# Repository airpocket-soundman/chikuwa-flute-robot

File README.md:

# ちくわ笛ロボット 強化学習環境(Arduino Physical AI チャレンジ 2026)

作品アイデア「[口笛を真似るちくわ笛ロボット](https://airpocket-soundman.github.io/maker_contest_2026/ideas/chikuwa-flute-imitation-robot/)」のための、シミュレーター・強化学習環境・学習スクリプトです。

プロジェクト全体の進め方(6 段階)と現状は [docs/roadmap.md](docs/roadmap.md) にまとめています。

> **現在の計画と結果（2026-09-24）:** 最新の構成は「**未知の機体を約9秒の較正で知り（デジタルツイン）、決定論の制御を骨格にして NN が補正と先回りを足し、同じ曲を繰り返して上手くなる**」です。
> シミュレーターの固定ベンチマーク（未知の機体32台・参照10曲）で、命中率（±25 cent・0.3 s以内）は 1回目 92 %、3回目 93 %（決定論＋ツイン 80 %、位置センサー付きの参考値 82 %）。お手本の音声を NN が聴いて覚えた目標でも 2回目 90 %。実機は未検証。
> - 計画と結果のページ: [yamabiko-plan.html](https://airpocket-soundman.github.io/chikuwa-flute-robot/yamabiko-plan.html)（決定論との比較と、曲・機体・方式を選べるシミュレーションつき）
> - 計画書: [docs/fitting-twin-plan.md](docs/fitting-twin-plan.md) ／ 実機の手順書: [docs/real_rig_runbook.md](docs/real_rig_runbook.md)
> - 主なコード: `flute_rl/yamabiko/fitting.py`（較正とツイン）、`residual_performer.py`（骨格＋NN補正）、`residual_numpy.py`（UNO Q 用の numpy 版）、`device.py`（ブラックボックス／実機の窓口）
> - これまでの試行の記録: [e2e-training-report.html](https://airpocket-soundman.github.io/chikuwa-flute-robot/e2e-training-report.html)。以下の各節はその経緯で、数値は当時のものです。

> **E2E方針（2026-09-21）:** 新しい本命経路では、YINによる音程列、物理式、固定バルブルールを推論から外し、
> 1個のモデルが生のお手本音声と生の自己音声からPWM・バルブ・終了を直接出します。
> 実装と学習手順は [docs/e2e.md](docs/e2e.md)、モデルは `flute_rl/yamabiko/e2e.py`、
> 学習は `scripts/train_yamabiko_e2e.py`、実機推論は `scripts/yamabiko_e2e_play.py` です。
> 推論経路、学習済みシミュレーターチェックポイント、NumPy書き出し、テストを実装済みです。実機評価はまだありません。
> コンテストでは、**生音声の知覚 → 物理的な行動 → 実際に鳴った生音声 → 同じモデルの内部状態の適応**という
> 閉ループ全体をフィジカルAIとして示します。笛を交換して一度崩れ、同じ重みのまま吹くほど再適応するデモを中心にします。
> UNO QではPyTorchを使わず、64,206パラメーターのモデルを約245KiBのNumPy形式へ書き出します。
> 機能優先のPC基準モデルは812,822パラメーター（約2.94MiB）で、成功後に小型版へ蒸留します。
> MCUの16kHz PCMストリームから毎10ms、最新20msを直接入力し、YINは実行しません。
> マイク・室内音響も乱数化した未学習4 seed・各64条件（合計256条件）では、音程誤差が平均 **271.6 → 277.0 → 307.6セント**、
> 自己音を遮断すると **294.3 → 326.4 → 379.3セント**です。従来モデルの乱数化時平均387.9セントから285.4セントへ改善し、閉ループ利得も平均48.0セント再現しました。反復ごとの単調な上達はまだ未達です。
> モデル構造、強化学習、採否を含む評価は [HTMLレポート](docs/e2e-training-report.html) に図解しています。
> 公開版は [GitHub Pages の段階別学習レポート](https://airpocket-soundman.github.io/chikuwa-flute-robot/e2e-training-report.html) で、各Gateの前後WAVを再生できます。

> **テーマの変更(2026-09-17): やまびこ1号。** 笛の音程を直動軸の位置センサーに使い、エンコーダーなしで位置制御する。
> 機体の違いは再帰的なモデルの記憶の中だけで覚え、吹くほど合ってくる。設計・実装・学習なしの結果は
> [docs/yamabiko.md](docs/yamabiko.md)、コードは `flute_rl/yamabiko/` と `scripts/yamabiko_*.py`。
> 以下の内容(エッジに吹き付ける笛、結果 1〜5)は旧テーマのもので、再現できるよう残しています。

- **numpy だけで動きます**(PyTorch などは不要)。Arduino UNO Q の Linux 側(Debian / Cortex-A53)でそのまま動かす前提です
- gymnasium が入っていれば `gymnasium.Env` として動作し、入っていなければ同じ API の簡易版で動きます(gymnasium 経由での動作確認はまだしていません)

## 構成

```
chikuwa-flute-robot/
├─ docs/
│  ├─ idea.md               作品アイデアのページ(元は maker_contest_2026 のアイデア集)
│  └─ uno_q_model_design.md UNO Q 向けモデル設計メモ
├─ flute_rl/
│  ├─ sim.py       物理シミュレーター(管の共鳴・リニアアクチュエーター・SCS0009・発音の窓・測定ノイズ)
│  ├─ targets.py   お手本の自動生成(カリキュラム)と、口笛の音程軌跡からの変換
│  ├─ env.py       強化学習環境(1 テイク / 複数テイク / フィードバック)と評価ツール
│  ├─ baseline.py  物理モデルだけで作った基準コントローラー(学習の出発点)
│  ├─ adapt.py     テイク間の機体推定(前のテイクの録音からアクチュエーターの速さ・管長を当てはめる)
│  ├─ policy.py    numpy の MLP 方策と、基準コントローラー + 残差の方策
│  └─ pitch.py     YIN による音程抽出(口笛入力・録音の解析用)
├─ scripts/
│  ├─ train_residual_es.py  機体推定つきコントローラーの上に残差方策を ES で学習(並列)
│  ├─ compare.py   コントローラーをテイクごとに比較(信頼区間つき)
│  ├─ train_es.py  進化戦略(ES)で残差方策を学習(旧版)
│  └─ bench.py     各処理の所要時間を測る(UNO Q 実機で実行する用)
└─ tests/          pytest
```

## すぐ試す

```bash
cd chikuwa-flute-robot
python -m pytest -q
python scripts/compare.py --takes 5 --episodes 100 --workers 8
python scripts/train_residual_es.py --feedback --takes 2 --gens 200 --pop 96 --episodes 8 --workers 8 --out runs/feedback.npz
python scripts/bench.py
```

## 環境の仕様

| 項目 | 内容 |
|---|---|
| 時間の刻み | 10ms / ステップ |
| 行動 | `[プランジャーの PWM, 吹き込み角度]`、どちらも -1〜+1(角度は ±15° に対応) |
| エピソード | お手本 1 本を `takes` 回吹く。テイクの間はプランジャーを原点に戻す |
| 風量 | 一定(モデル化していない) |

### お手本(学習用の曲)

`flute_rl/targets.py` の `make_target` が自動で作ります。演奏難易度の高すぎる曲は作りません。

| 決まり | 値 |
|---|---|
| 1 音の長さ | 0.25 秒以上(0.25 / 0.3 / 0.4 / 0.6 / 0.8 秒から選ぶ) |
| 隣の音との跳躍 | 400 セント(長 3 度程度、プランジャー約 20mm)まで |
| 奏法 | 1 曲ごとに「つなげる(スラー・同じ高さはタイ)」「切る(音の間に 50〜120ms の無音)」「混ぜる」のどれか |
| 種類(難易度順) | 1 音 → 2 音 → 2 音のグライド → 短いメロディ → ビブラートつきメロディ |

「切る」は、吹き込み角度を鳴る範囲の外に振って音を止める動きで表現します。無音の区間で鳴ると罰(`-1`)、音符で鳴らないと罰(`-2`)なので、この動きも学習の対象です。評価では、音符の間の短い無音で鳴ってしまった割合を `gap_leak` として出します。

学習では、あらかじめ作った 1,000 曲のセット(`runs/target_bank.npz`、`train_residual_es.py --bank 1000` で自動作成)から毎世代 8 曲を選んで使い回します。評価用の曲は別の乱数で作るので、学習用と重なりません。セットの中身は WAV と図で確認できます:

```bash
python scripts/export_targets.py --bank runs/target_bank.npz --count 20 --out runs/target_preview
```

### 学習する方策のネットワーク

`train_residual_es.py --feedback` で、演奏中に遅れて届く音程を使う方策を学習します。ネットワークは 3 種類から選べます。

| 指定 | 構造 | 狙い |
|---|---|---|
| `--arch mlp` | 記憶なし(今の観測だけ) | 基準 |
| `--arch mlp --history 10` | 直近 10 ステップの「聞こえたずれ・自分の PWM・角度」を窓で渡す | 遅れの情報だけを与える対照 |
| `--arch gru --hidden 16` | リカレント(GRU)。状態は曲の最初に 1 回だけ初期化し、テイクをまたいで持ち越す | 自分の指令が何ステップ後に聞こえるか(個体ごとに違う遅れ)を記憶から学ぶ |

どれも出力は「行動への補正(PWM・角度)」と「聞こえた音をどれだけ信じるか(フィードバックの強さ 0〜2 倍)」です。`scripts/trust_analysis.py` で、方策が場面ごと(休符・音の出だし・音を伸ばしている間)・遅れの長さごとにどれだけ耳を信じているかを集計できます。

### 観測

演奏中は音を聴かずに流し切る前提(案 2)なので、**標準ではリアルタイムの音程は観測に入りません**。

| ブロック | 内容 |
|---|---|
| `target` / `target_mask` | お手本の音程(今から `lookahead` ステップ先まで)と、音があるかどうか |
| `act_hist` | 直近 `history` ステップの自分の行動 |
| `travel` | 自分の PWM 指令を積算した移動量の目安 |
| `angle_readback` | SCS0009 の読み返し角度 |
| `angle_comp` | 発音補償で見つけた「鳴る角度」(唯一のキャリブレーション) |
| `time` | テイク内の経過割合 |
| `prev_err` / `prev_mask` / `prev_act` / `take` | (`takes > 1` のとき)前のテイクの音程のずれと行動。テイクを重ねて上達するための情報 |
| `fb_err` / `fb_heard` / `fb_valid` | (`feedback=True` のとき)`obs_delay` ステップ遅れて届く音程のずれ |

### 報酬(ステップごと)

| 項目 | 値 |
|---|---|
| 音程誤差 | `-min(|ずれ[セント]|, 300) / 100`(鳴るべき区間で、音程が測れたとき) |
| 無音 | 鳴るべき区間で鳴っていない: `-2` |
| 休符中の発音 | `-1` |
| 裏返り(オクターブ上) | `-1` を追加 |
| 行動の急変 | `-0.01 × |Δ行動|²` |

### ドメインランダム化(`FluteParams.sample`)

| 分類 | 項目(公称値 ± 幅) |
|---|---|
| 笛 | 管長 150±10mm、開口端補正 5±2mm、窓の位置 0±4°、窓の幅(下側 5±1.5° / 上側 4±1.5°)、窓の狭まり方、角度による音程変化 10±5 セント/°、裏返り開始位置 |
| 駆動 | 速さ 150±30mm/s(向き別)、不感帯 0.20±0.08、速度の時定数 30±15ms、指令遅れ 0〜2 ステップ、ガタ 0.3±0.2mm |
| サーボ | 速度 600±100°/s、時定数 20±10ms、刻み 300°/1024(固定) |
| 環境・測定 | 気温 25±10℃(約 3 セント/℃)、音程推定ノイズ 3±2 セント、推定の欠落 0〜4%、フィードバック遅れ 1〜5 ステップ |

値はすべて仮です。3D プリント笛・ちくわ・実機のアクチュエーターを実測して置き換えます。

## 結果 2: テイク間の機体推定(PC、2026-09-15)

`scripts/compare.py` で、学習・調整に使っていない 100 条件(カリキュラム進度 0.8)をテイクごとに比較。音程のずれの平均(セント)、[ ] は 95% 信頼区間。

| コントローラー | 1 テイク目 | 2 テイク目 | 3 テイク目 | 4 テイク目 | 5 テイク目 |
|---|---|---|---|---|---|
| 物理モデルだけ | 165 | 165 | 165 | 165 | 165 |
| 古典 ILC(ゲイン 0.7) | 165 | 69.3 [58, 83] | 38.6 [30, 48] | 30.7 [24, 39] | 26.2 [21, 33] |
| **機体推定 + ILC(`AdaptivePolicy`)** | 165 | **23.4 [19, 28]** | **22.6 [19, 27]** | **20.8 [17, 26]** | **20.3 [16, 25]** |
| 機体推定 + ILC + 残差方策(ES) | 167 | 22.0 [18, 26] | 21.9 [17, 27] | 21.9 [16, 29] | 21.4 [16, 28] |

古典 ILC との対応ありの差(機体推定 + ILC): 2 テイク目 **-45.9 セント [-58, -36]**、3 テイク目 -16.0 [-23, -10]、5 テイク目 -5.8 [-9, -3]。どのテイクでも信頼区間が 0 をまたがず、有意に良い。

仕組み(`flute_rl/adapt.py`):

- 1 テイク目のずれの大半は、**その個体のアクチュエーターの速さと管長を知らないこと**が原因だった(真のパラメーターを知っている物理モデルなら 1 テイク目でも約 40 セント)
- そこで、吹き終わった後に「自分が送った PWM」と「録音した音程」から、押し込み・引き戻しの速さ、管長、音程のずれを当てはめる(粗いグリッド探索 → ガウス・ニュートン法、外れ値の閾値を段階的に絞る)。推定した速さと真の速さの相関は約 0.96
- 次のテイクは推定したパラメーターで物理モデルを動かし、残りのずれを ILC で詰める
- 計算は numpy だけ・数十 ms で、テイクの合間に UNO Q の Linux 側で実行できる

強化学習(残差方策)について:

- 機体推定の上に残差方策(2,146 パラメーター)を並列 ES(96 候補 × 8 エピソード × 200 世代)で学習したが、**改善は 2 テイク目で -1.4 セントにとどまり、1 テイク目は +2 セント悪化**。演奏中に音を聴かない方式では、機体推定の後に残るずれは主に音の切り替わり(アクチュエーターの速さの物理的な限界)で、方策で詰められる余地が小さかった
- 前回 ES が失敗したのは、観測できない個体差(1 テイク目で ±200 セント)が評価のばらつきを支配していたため。機体推定でこれを取り除いてから学習すると、学習は安定する(悪化しない)が、伸びしろ自体が小さい

## 結果 3: 演奏中に聞いて直す方策(強化学習)

演奏中に `obs_delay` ステップ遅れて届く音程のずれで、プランジャーの推定位置を直す(`flute_rl/feedback.py`)。手作りの補正(`FeedbackPolicy`)の上に、「行動への補正」と「聞こえた音をどれだけ信じるか(補正の強さ 0〜2 倍)」を出すネットワークを ES で学習した。ネットワークは 3 種類(記憶なし MLP / 直近 10 ステップの履歴つき MLP / GRU)。お手本は 1,000 曲の固定セット(奏法の区別あり)、100 世代で打ち切り。

`scripts/compare.py --feedback --takes 3 --episodes 200`(学習に使っていない 200 条件)、音程のずれの平均(セント):

| コントローラー | 1 テイク目 | 2 テイク目 | 3 テイク目 |
|---|---|---|---|
| 物理モデルだけ | 165 | 165 | 165 |
| 古典 ILC(ゲイン 0.7) | 165 | 71 | 37 |
| 機体推定 + ILC | 165 | 19 | 18 |
| 機体推定 + 演奏中の補正(手作り) | 62 | 23 | 22 |
| + 強化学習(記憶なし MLP) | 44 | 20 | 20 |
| + 強化学習(履歴つき MLP) | **38** | 19 | 20 |
| + 強化学習(GRU) | 44 | **17** | **17** |

- 演奏中に聞くことで初めて 1 テイク目が直せる。強化学習は手作りの補正に対して 1 テイク目で約 20 セント良い(対応ありの差の信頼区間は 0 をまたがない)
- 3 種類のネットワークの差は小さく、記憶(GRU)の効果ははっきりしなかった
- 強化学習の方策は音が出ている割合が少し下がる(GRU で 0.99)。報酬の上では、大きくずれるより黙るほうが罰が軽いため

## 結果 4: 厳しめのシミュレーター(`harsh`)

聞き比べでどの方式も合格に聞こえたことから、シミュレーターが甘すぎるという指摘を受けて見直した。制御側はシミュレーターと同じ形の式を持っていて、機体推定は「値だけ違う」機体を当てはめていた。そこで、制御側が知らない効果を `FluteParams.sample(harsh=...)` で入れられるようにした:

| 分類 | 効果(`harsh=1` での範囲。すべて推測の値) |
|---|---|
| モーター | 静止摩擦(動き出しに PWM が +0〜0.15 余分に要る)、PWM と速さの非線形(指数 0.7〜1.5)、差し込むほど遅くなる(0〜30%)、演奏中の速さの揺らぎ、動きの雑音(0〜10%)、指令が 1 ステップ遅れる確率(0〜15%)、ガタ +0〜0.7mm |
| 鳴る角度 | 鳴り始めの遅れ(20〜80ms)、鳴り始めの窓が鳴り続ける窓より各側 0〜1.5° 狭い(ヒステリシス)、窓の端で確率的に音が切れる、最適な角度が差し込み量で ±3° 動く、息による音程の揺らぎ(0〜8 セント)、裏返りやすさ |
| 聞き取り | 音程の推定がオクターブずれる確率(0〜5%) |

`harsh=0` なら以前とまったく同じ機体・動きになる(テストで確認)。学習し直さずに `--harsh 1.0` で評価した結果(同じ 200 条件、**実際に鳴った音程**のずれの平均):

| コントローラー | 1 テイク目 | 2 テイク目 | 3 テイク目 |
|---|---|---|---|
| 物理モデルだけ | 172 | 174 | 173 |
| 古典 ILC(ゲイン 0.7) | 172 | 113 | 88 |
| 機体推定 + ILC | 172 | 48 | 50 |
| 機体推定 + 演奏中の補正(手作り) | 77 | 35 | 36 |
| + 強化学習(記憶なし MLP) | 59 | 27 | 28 |
| + 強化学習(履歴つき MLP) | 57 | 28 | 32 |
| + 強化学習(GRU) | 56 | 25 | 30 |

- 甘いシミュレーターと比べて、2 テイク目のずれは 1.5〜2.5 倍になり(機体推定 + ILC で 19 → 48 セント)、テイクを重ねても良くならなくなった。これまでの結果は、シミュレーターの甘さに助けられていた
- それでも順位は変わらず、機体推定・演奏中の補正・強化学習のそれぞれに効果は残っている
- 最初は測った音程(音程推定のオクターブ誤りを含む)で評価していて、2 テイク目を 58〜79 セントと大きく見積もっていた。上の表は実際に鳴った音程で数え直したもの
- 厳しいシミュレーターでの学習し直しは GPU 版(`scripts/train_es_gpu.py --harsh 1.0`)で進めている

## 結果 5: 厳しいシミュレーターでの学習し直しと、耳で聞く方策(E2E 方法 A)

`scripts/train_es_gpu.py --harsh 1.0` で 3 つの方策を 100 世代学習し直した(甘い機体で学習したモデルから開始)。E2E の方法 A(`--hearing runs/pitchnet_self.pt`)では、シミュレーターの中で笛の音を鳴らし(8kHz、`flute_rl/torch_audio.py`)、学習済みの耳のネットワークで `obs_delay` 遅れて聞かせる。演奏中の補正と機体推定には耳が聞き取った音程を使い、方策には耳の自信の度合いと特徴の要約(PCA 16 次元)も渡す。

`scripts/compare_gpu.py --harsh 1.0 --takes 3 --episodes 200`(学習に使っていない 200 条件)、**実際に鳴った音程**のずれの平均(セント)。( ) は測った音程でのずれ(音程推定のオクターブ誤りを含む):

| コントローラー | 1 テイク目 | 2 テイク目 | 3 テイク目 | 音が出ている割合 |
|---|---|---|---|---|
| 手作りの補正(測定値で聞く) | 73.7 (104.0) | 35.4 (66.6) | 34.5 (64.9) | 0.96 |
| 手作りの補正(耳で聞く) | 79.7 (109.6) | 36.4 (65.4) | 35.1 (67.5) | 0.96 |
| 甘い機体で学習: 記憶なし MLP / 履歴つき MLP / GRU | 58.6 / 56.9 / 56.4 | 26.5 / 27.7 / 25.2 | 28.0 / 31.6 / 29.9 | 0.94 / 0.93 / 0.92 |
| 学習し直した後: 記憶なし MLP | 58.4 | 31.1 | 32.2 | 0.96 |
| 学習し直した後: 履歴つき MLP | **53.6** | **24.9** | **26.7** | 0.96 |
| 学習し直した後: GRU | 56.0 | 26.4 | 30.5 | 0.96 |
| 学習し直した後: GRU(耳で聞く、方法 A) | 62.3 | 26.9 | 28.0 | 0.96 |

学習し直した履歴つき MLP は、手作りの補正に対して 1〜3 テイク目で -20.1 / -10.5 / -7.8 セント(対応ありの差、信頼区間は 0 をまたがない)。

- 耳は測定値の代わりに使える(手作りの補正で比べて、差は信頼区間の範囲内)
- 学習し直しの伸びは約 3 セントと小さい。変わったのは、黙って点を稼ぐ癖が消えたこと(音が出ている割合が 0.96 に戻った)
- 耳の特徴を渡しても(方法 A)、はっきりした効果はなかった
- `scripts/trust_analysis.py --harsh 1.0` で見ると、GRU は耳を信じる度合いを場面や遅れによらず約 1.8 倍にしているだけ
- 厳しい効果を 1 つずつ入れて調べると、測った音程のずれを押し上げていた最大の要因は**音程推定のオクターブ誤り**だった(2 テイク目 26 → 56 セント)。これは実際に鳴った音のずれではなく、測り間違い。以前は測った音程で評価していたので、厳しいシミュレーターのずれを大きく見積もっていた(今は実際に鳴った音程で評価する)
- 制御側が乱数を使わない厳しい効果(不感帯・静止摩擦・非線形・差し込み量で変わる速さ)の真の値を知っていても、2 テイク目の改善は 8〜9 セントまで。機体推定のモデルを広げる伸びしろは限られる
- 次は、実物の測定でシミュレーターを合わせ込むこと

## 実物の笛でシミュレーターを合わせ込む

シミュレーターの値は今はすべて推測なので、3D プリント笛(やちくわ)を測って置き換える。録音は WAV(16bit か 32bit の PCM)。スマホの録音は `ffmpeg -i rec.m4a -ac 1 -ar 48000 take.wav` などで変換する。

**1. 1 本の録音を調べる**(何 Hz で鳴っているか、倍音か):

```bash
python scripts/analyze_recording.py take.wav --tube-mm 60 --bore-mm 10 --temp 25
```

**2. 差し込み量を変えて測る(管の合わせ込み)**: 底(プランジャーや詰め物)の差し込み量を 5〜10mm ずつ変え、同じ吹き方で 1 本ずつ録音する。`depth_mm,ファイル名` の CSV を作って:

```bash
python scripts/calibrate.py tube sweep_depth.csv --bore-mm 10
```

管の実効長と音速(気温の目安)、各点のずれ(セント)と、`FluteParams` の `tube_len` / `end_corr` / `temp_c` の値を出す。

**3. 角度を変えて測る(鳴る角度の合わせ込み)**: 差し込み量を固定し、吹き込む角度を 0.5〜1° ずつ変えて録音する。`angle_deg,ファイル名` の CSV を作って:

```bash
python scripts/calibrate.py window sweep_angle.csv
```

鳴る範囲の端と中心、角度 1° あたりの音程の変化(`theta_opt_deg` / `win_lo_deg` / `win_hi_deg` / `k_theta`)を出す。

**4. PWM を変えて動かす(アクチュエーターの合わせ込み)**: 笛を鳴らしたまま、一定の PWM でプランジャーを動かして録音する。PWM を何段階か変えて(押し込む向きと引き戻す向きは別々に)、`pwm,ファイル名` の CSV を作る。2 の結果(実効長と音速)を渡して:

```bash
python scripts/calibrate.py actuator sweep_pwm.csv --acoustic-mm 150.5 --sound-speed 346.4
```

音程の変化を位置の変化に直して速さを求め、最大の速さ・不感帯・PWM と速さの非線形(`v_max_in` / `deadband` / `pwm_curve`)を出す。

どれも、シミュレーターで作った「答えの分かっている録音」から値を取り戻せることをテストで確かめてある(`tests/test_calibrate.py`)。

## 段階 2・3 の準備(小さくする、マイコンで動かす)

実機がなくても PC でできるところまで進めた。UNO Q の実機では、どれもまだ試していない。

| 項目 | 内容 | 結果 |
|---|---|---|
| 方策の int8 化 | `scripts/quantize_policy.py`。行列ごとに 1 つのスケールで int8 にし、C のヘッダーを書き出す | 履歴つき MLP(3,267 パラメーター)が 3,380 バイトに収まる。厳しい機体 200 台で float32 との差は 0.0 ± 0.1 セント |
| 小さい耳 | `PitchNet(width=8, pool=4)`、20 セント刻み | 16,131 パラメーター、1 フレーム 0.18M 回の積和(大きい耳は 250,277 / 2.41M)。合成音で誤差の中央値 1.0 セント(大きい耳 0.9、YIN 3.1)。10ms ごとに動かすと 1 秒あたり約 1,800 万回の積和で、マイコンの CPU の 1 割前後の見込み(実機で要計測) |
| 制御の C 版 | `mcu/controller.{h,c}`、`mcu/policy_mlp.{h,c}` | 物理モデル・演奏中の補正・ILC・int8 の方策を 1 台分。機体推定はテイクの合間に Linux 側で行い、値だけ渡す。雑音のない機体で numpy 版と同じ行動(テスト) |
| HIL の通信 | `mcu/hil_protocol.{h,c}`、`scripts/hil.py` | テイクの頭にお手本・前回のずれ・推定した機体をまとめて送り、10ms ごとには 13 バイトずつやり取りする(115200 baud で約 2.3ms)。PC 上の代役(`mcu/hil_host.c`)を相手に、numpy 版と同じ演奏になる(テスト) |
| Arduino スケッチ | `mcu/uno_q_hil/uno_q_hil.ino` | 実機未確認。どのシリアルが PC や Linux 側につながるかは、実機で確かめる必要がある |

```bash
python scripts/quantize_policy.py runs/harsh_hist.npz --out runs/harsh_hist_int8
python -m ziglang cc -O2 -Imcu -Iruns -DHIL_NET_HEADER='"harsh_hist_int8.h"' -DHIL_NET=HARSH_HIST_INT8 mcu/hil_host.c mcu/hil_protocol.c mcu/controller.c mcu/policy_mlp.c -o runs/hil_host.exe
python scripts/hil.py --link process:runs/hil_host.exe --history 10 --harsh 1.0
```

C のテストには、C コンパイラーの入った `ziglang`(`pip install ziglang`)を使う。

## GPU 版(`flute_rl/torch_sim.py`、`flute_rl/torch_env.py`)

多数の機体をまとめて 1 ステップずつ進める版。雑音のない機体では、行動が numpy 版と 1 ステップずつ一致する(GRU を含む)。1 世代 768 回の演奏では CPU 20 コアの numpy 版とほぼ同じ速さ(約 6 秒)で、候補を 10 倍にすると 1 秒あたりの演奏数が約 2.3 倍になる。細かい計算の呼び出しが時間を決めているので、さらに速くするには計算をまとめる工夫が要る。

開発の経緯と、世代ごとの演奏の聞き比べは [docs/history.html](docs/history.html) にある。

## 結果 1: 最初の実験(PC、2026-09-15 時点)

ランダム化した 20 条件(カリキュラム進度 0.8)での、音程のずれの平均(セント)。

| コントローラー | 1 テイク目 | 2 テイク目 | 3 テイク目 | 4 テイク目 | 5 テイク目 |
|---|---|---|---|---|---|
| 物理モデルだけ(`PhysicsPriorPolicy`) | 202 | 202 | 202 | 202 | 202 |
| + 古典 ILC、ゲイン 0.5(`ILCPolicy`) | 202 | 118 | 78 | 63 | 52 |
| + 古典 ILC、ゲイン 0.7 | 202 | 90 | 61 | 51 | 44 |
| + 古典 ILC、ゲイン 0.9 | 202 | 77 | 54 | 49 | 45 |
| 物理モデル + ES 残差(40 世代、学習率 0.03) | 333 | 175 | 298 | - | - |
| ILC(ゲイン 0.7)+ ES 残差(25 世代、学習率 0.005、σ 0.02) | 212 | 82 | 61 | - | - |

分かったこと:

- アクチュエーターの速さの個体差(±20%)があると、音を聴かずに推測で動かすだけでは 1 テイク目が平均 200 セントずれる。1 テイク目の中ではこの個体差を知る手段がない
- 前のテイクのずれを観測に入れれば、古典的な ILC だけでもテイクごとに上達する(5 テイクで 202 → 44 セント)。環境の設計どおりに動いている
- **ES による残差方策の学習は、最初の設定では失敗した**(物理モデルより悪化)。評価のばらつき(1 候補あたり 4 エピソード)に対して更新が大きすぎたと考えられる。学習率・ノイズを下げ、出発点を ILC にした再学習では悪化はしなくなったが、ILC だけ(202 / 90 / 61)と比べて**有意な改善もなかった**(2 テイク目がわずかに良く、1 テイク目がわずかに悪い程度で、評価のばらつきの範囲)
- 今の ES(1 世代 16 候補 × 数エピソード)では、7,400 パラメーターの方策を動かすには評価が粗すぎる。次の手は、候補数・エピソード数を増やして並列化する、観測を絞って方策を小さくする、ILC のゲインなど数個のパラメーターだけを学習させる、のいずれか

## 次にやること

- 実機ログから `FluteParams` を当てはめる(世界モデルの実測合わせ)と、残差モデルの追加
- フィードバック補正方策(`feedback=True`)の学習と、MCU に載せる小型化
- 口笛の録音 → `pitch.pitch_track` → `targets.from_pitch_track` → 方策、の一連の流れを実機で通す

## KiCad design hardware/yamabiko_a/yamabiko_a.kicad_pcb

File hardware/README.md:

# やまびこ1号の基板（KiCad 10）

| フォルダ | 中身 |
|---|---|
| `yamabiko_a/` | **A 基板**: UNO Q の R3 ヘッダーに挿す Arduino シールド（外形は Arduino Uno、ねじ穴なし）。リニアアクチュエーター（TB6643KQ）、ファン（ハイサイドスイッチ、PWM、タコ）、SCS0009（6 V レギュレーター、半二重バッファ）、控えの電磁弁、演奏開始ボタン |
| `yamabiko_b/` | **B 基板**: UNO Breakout Carrier の J14 / J15 に載せるマイク基板。ICS-43434 を MCU の SAI1（3.3 V）へ、予備で MI2S0（1.8 V）へ。**J14 の左には何も出さない**（UNO Q が載る）: 基板の左端は J14 のすぐ外で切り、部品は J15 の右に並べて、Carrier の右端から 13 mm はみ出す。マイクの L/R は GND 固定（左スロット）。予備に I2C（J15-16 / 18 = PF14 / PF15、4.7 kΩ プルアップ）と ADC / GPIO（PA0 / PA1 / PA3）を XH で出す |
| `lib/` | プロジェクトのシンボルとフットプリント（TB6643KQ、ピン番号 1 = G / 2 = D / 3 = S の FET） |
| `gen/` | 上の 2 つを作るスクリプト |

部品はすべて秋月電子通商のスルーホール品、コネクターは XH。部品表と IO 仕様は公開ページにまとめてある
（部品表: <https://claude.ai/artifact/Dvwt1oD2amMsziMAJQZxBU>、IO 仕様: <https://claude.ai/artifact/3YuJc5qp5sogrEiBCrkaD5>）。

## 作り方

回路図と基板は手で描いていない。**`gen/design.py` の部品・ネット・配置が正**で、そこから生成する。

```
gen/build.sh FREEROUTING.jar REPORT_DIR
```

1. `gen_boards.py`（KiCad の Python）: `design.py` から回路図を書き、KiCad にネットリストを出させて `design.py` と照合してから、
   同じネットで基板を作る。A 基板の外形と R3 ヘッダーの位置は KiCad の `Arduino_Uno` テンプレートのもの
2. `route.py`: Specctra DSN を書き出して [Freerouting](https://github.com/freerouting/freerouting)（v2.4.1 を使用。リポジトリには入れていない）で自動配線し、
   結果を取り込んで両面に GND ベタを張る
3. `finish_route.py`: Freerouting が残した接続があれば、2 層の格子上の A* で引く
4. `check.sh`: ERC、DRC（回路図との一致を含む）、配置図

版だけ上げるときは、`design.py` の `REV` を変えて `gen/add_title.py yamabiko_a/yamabiko_a.kicad_pcb` を KiCad の Python で実行すれば、配線し直さずにシルクの版の表記だけ入れ替わる（回路図の表題欄の rev は手で直す）。

シルクには全部品の部品番号と、抵抗・コンデンサの値を入れる（電解コンデンサは容量だけ。耐圧は部品表）。XH コネクターと SW1 は部品番号に接続先の名前を添え（例: `J3 FAN`）、コネクターは各パッドの脇にピン名を入れる（`design.py` の `device` / `pin_names`）。UNO Q のヘッダー J101〜J104 の番号はシルクに出さない。基板名と版（`Yamabiko No.1 A Rev 1.0` など。版は `design.py` の `REV`）も表面のシルクに入れ、部品・パッド・シルク・基板の端から離れた空きのうち、基板の中央にいちばん近いところに置く（入る最大の文字サイズで、入らなければ 2 行）。文字の位置は `gen_boards.py` が部品ごとに上下左右などの候補から、パッド・シルクの図形・ほかの文字・基板の端と重ならないところを選ぶ。

生成した時点の結果（2026-09-18）: 両基板とも ERC 0、DRC のエラー 0、未接続 0、回路図との不一致 0。
警告は A 基板で、シルクが基板の端に近い 2 件と、R8 / R9 の値がヘッダー J101 の枠線にかかる 2 件、GND ベタのサーマルの本数。

KiCad の Python（pcbnew）には落とし穴がある: 読み込んだ基板から `Remove` すると、そのプロセスではそれ以降の SWIG の
ラッパーが壊れる（`SwigPyObject` が返る）。スクリプトはすべて、削除を pcbnew ではなくファイル側で行う。
また、基板を保存すると `.kicad_pro` が既定のネットクラスで上書きされるので、プロジェクトファイルは基板の後に書く。

## 発注（JLCPCB）

`gen/fab.sh` がガーバーとドリルを出して、基板ごとに zip にまとめる（`fab/yamabiko_a_gerber.zip`、`fab/yamabiko_b_gerber.zip`）。
出す前にベタを塗り直し、シルクはレジストの開口で切る。JLCPCB にはこの zip をそのまま上げる。

| | A 基板 | B 基板 |
|---|---|---|
| 大きさ | 68.6 × 53.3 mm（Arduino Uno 形、角の面取りあり） | 40.7 × 53.3 mm |
| 層 | 2 | 2 |
| 最小の線幅 / 間隔 | 0.3 / 0.2 mm | 0.3 / 0.2 mm |
| 最小の穴 | 0.4 mm（ビア 0.8 mm、4 個） | 0.8 mm（ビアなし） |
| 長穴 | DC ジャック J1 に 3 個 | なし |

ほかは JLCPCB の既定（厚み 1.6 mm、有鉛 HASL でも無鉛でも可、レジストの色は自由）でよい。
KiCad で基板を直したら `gen/check.sh` を通してから `gen/fab.sh` をやり直す。

## 組み立ての注意

- **A 基板の R3 ヘッダー**: 3D 表示では上向きに立っているが、実物はオスのピンヘッダーを上から挿してピンを下に出し、UNO Q のソケットに挿す
- **B 基板の J14 / J15**: 3D 表示ではオスヘッダーだが、実物は **2×20 のメスのピンソケットを裏（下面）に付けて** Carrier の J14 / J15 にかぶせる。
  パッドの並びは Carrier の上面図と同じ（上から見て奇数ピンが左列、1 番ピンが上端）
- **B 基板の J2 は 1.8 V**（MI2S0）。3.3 V の線をつながない
- **B 基板の予備 I2C（J3）** は PF14 / PF15。UNO Q の Arduino コアの既定の I2C4 は PD12 / PD13 なので、使うときはピンの割り当てを切り替える
- **TB6643KQ の裏の金属部分**は IC の GND（4 番ピン）とつながっている。4 番ピンは検出抵抗 R1 を通って GND に落ちるので、放熱器を付けるなら絶縁する
- **2N7000（Q2, Q3）** は足を 2.54 mm に広げて挿す（フットプリントが `TO-92_Inline_Wide`）
- 控えの電磁弁まわり（Q4, R15, R16, D1, J5）は DNP。必要になったら実装する

## まだ決めていないこと

- アクチュエーターの実際の電流（TB6643KQ の平均 1.5 A に収まるか）。検出抵抗 R1（0.1 Ω）の電圧で測れる
- U2（NJM7806FA）の放熱器。基板上に場所を取っていないので、まず放熱器なしで温度を見る

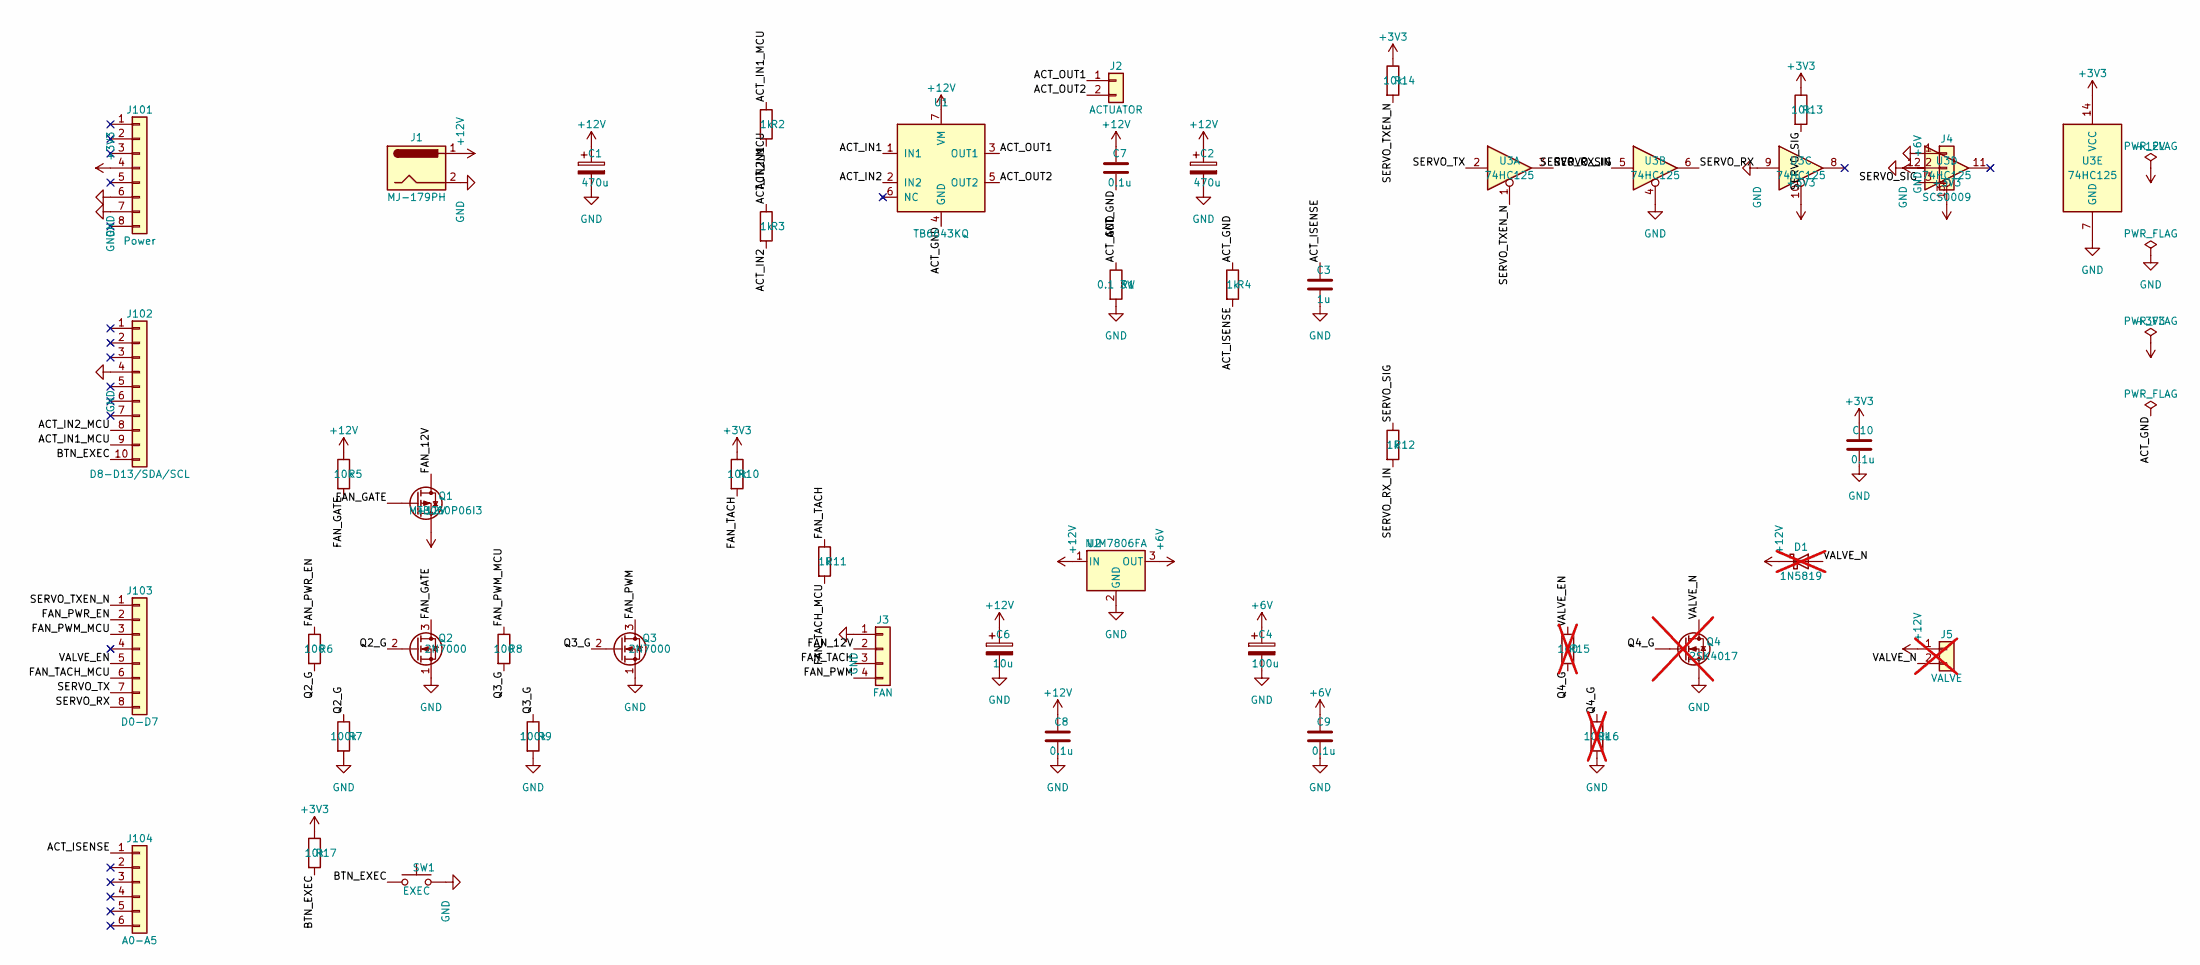
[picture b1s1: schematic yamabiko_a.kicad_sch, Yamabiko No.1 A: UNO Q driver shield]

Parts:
C1, C2: 470u; CP_Radial_D10.0mm_P5.00mm
C3: 1u; C_Disc_D5.0mm_W2.5mm_P5.00mm
C4: 100u; CP_Radial_D6.3mm_P2.50mm
C6: 10u; CP_Radial_D5.0mm_P2.00mm
C7, C8, C9, C10: 0.1u; C_Disc_D3.0mm_W1.6mm_P2.50mm
D1: 1N5819; D_DO-41_SOD81_P5.08mm_Vertical_AnodeUp; not fitted
J1: MJ-179PH; BarrelJack_Horizontal
J2: ACTUATOR; JST_XH_B2B-XH-A_1x02_P2.50mm_Vertical
J3: FAN; JST_XH_B4B-XH-A_1x04_P2.50mm_Vertical
J4: SCS0009; JST_XH_B3B-XH-A_1x03_P2.50mm_Vertical
J5: VALVE; JST_XH_B2B-XH-A_1x02_P2.50mm_Vertical; not fitted
J101: Power; PinHeader_1x08_P2.54mm_Vertical
J102: D8-D13/SDA/SCL; PinHeader_1x10_P2.54mm_Vertical
J103: D0-D7; PinHeader_1x08_P2.54mm_Vertical
J104: A0-A5; PinHeader_1x06_P2.54mm_Vertical
Q1: MTB060P06I3; TO-251-3_Vertical
Q2, Q3: 2N7000; TO-92_Inline_Wide
Q4: 2SK4017; TO-251-3_Vertical; not fitted
R1: 0.1 3W; R_Axial_DIN0516_L15.5mm_D5.0mm_P20.32mm_Horizontal
R2, R3, R4, R11, R12: 1k; R_Axial_DIN0207_L6.3mm_D2.5mm_P2.54mm_Vertical
R5, R10, R13, R14, R17: 10k; R_Axial_DIN0207_L6.3mm_D2.5mm_P2.54mm_Vertical
R6, R8: 100; R_Axial_DIN0207_L6.3mm_D2.5mm_P2.54mm_Vertical
R7, R9: 100k; R_Axial_DIN0207_L6.3mm_D2.5mm_P2.54mm_Vertical
R15: 100; R_Axial_DIN0207_L6.3mm_D2.5mm_P2.54mm_Vertical; not fitted
R16: 100k; R_Axial_DIN0207_L6.3mm_D2.5mm_P2.54mm_Vertical; not fitted
SW1: EXEC; SW_PUSH_6mm
U1: TB6643KQ; Toshiba_HSIP7_P2.54mm
U2: NJM7806FA; TO-220F-3_Vertical
U3: 74HC125; DIP-14_W7.62mm_Socket

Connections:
+3V3: C10.1, J101.4, R10.1, R13.1, R14.1, R17.1, U3.10, U3.13, U3.14 (VCC)
+6V: C4.1, C9.1, J4.2, U2.3 (OUT)
+12V: C1.1, C2.1, C6.1, C7.1, C8.1, D1.1 (K), J1.1, J5.1, Q1.3 (S), R5.1, U1.7 (VM), U2.1 (IN)
/ACT_GND: C7.2, R1.1, R4.1, U1.4 (GND)
/ACT_IN1: R2.2, U1.1 (IN1)
/ACT_IN1_MCU: J102.9, R2.1
/ACT_IN2: R3.2, U1.2 (IN2)
/ACT_IN2_MCU: J102.8, R3.1
/ACT_ISENSE: C3.1, J104.1, R4.2
/ACT_OUT1: J2.1, U1.3 (OUT1)
/ACT_OUT2: J2.2, U1.5 (OUT2)
/BTN_EXEC: J102.10, R17.2, SW1.1
/FAN_12V: J3.2, Q1.2 (D)
/FAN_GATE: Q1.1 (G), Q2.3 (D), R5.2
/FAN_PWM: J3.4, Q3.3 (D)
/FAN_PWM_MCU: J103.3, R8.1
/FAN_PWR_EN: J103.2, R6.1
/FAN_TACH: J3.3, R10.2, R11.1
/FAN_TACH_MCU: J103.6, R11.2
/Q2_G: Q2.2 (G), R6.2, R7.1
/Q3_G: Q3.2 (G), R8.2, R9.1
/Q4_G: Q4.1 (G), R15.2, R16.1
/SERVO_RX: J103.8, U3.6
/SERVO_RX_IN: R12.2, U3.5
/SERVO_SIG: J4.3, R12.1, R13.2, U3.3
/SERVO_TX: J103.7, U3.2
/SERVO_TXEN_N: J103.1, R14.2, U3.1
/VALVE_EN: J103.5, R15.1
/VALVE_N: D1.2 (A), J5.2, Q4.2 (D)
GND: C1.2, C2.2, C3.2, C4.2, C6.2, C8.2, C9.2, C10.2, J1.2, J3.1, J4.1, J101.6, J101.7, J102.4, Q2.1 (S), Q3.1 (S), Q4.3 (S), R1.2, R7.2, R9.2, R16.2, SW1.2, U2.2 (GND), U3.4, U3.7 (GND), U3.9, U3.12

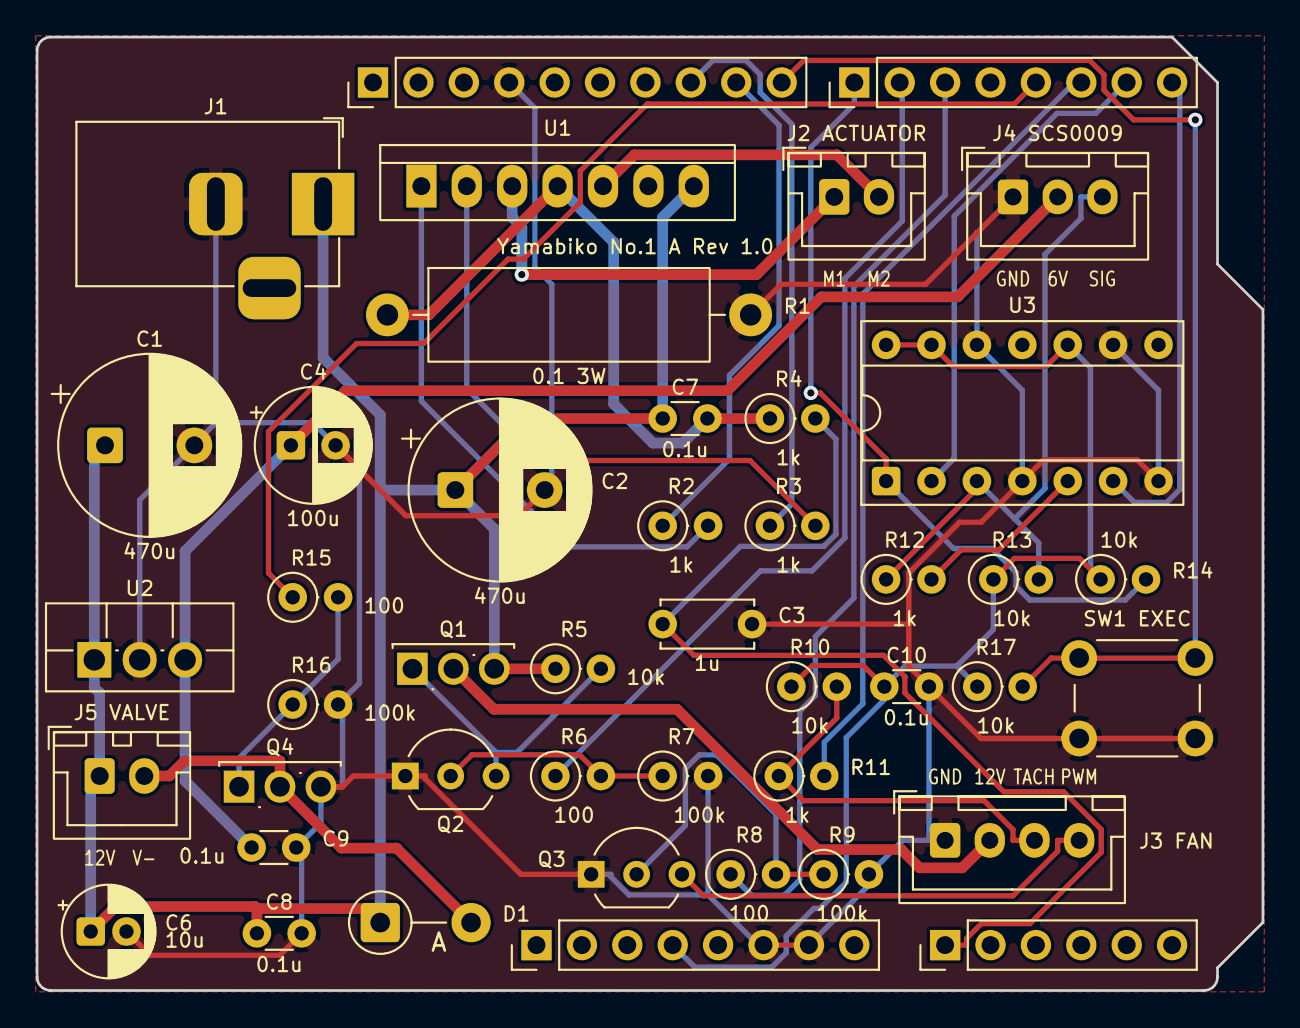
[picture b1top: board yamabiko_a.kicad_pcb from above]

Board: 2 copper layers, 68.6 x 53.3 mm, 44 parts (0 on the bottom side), 30 nets.

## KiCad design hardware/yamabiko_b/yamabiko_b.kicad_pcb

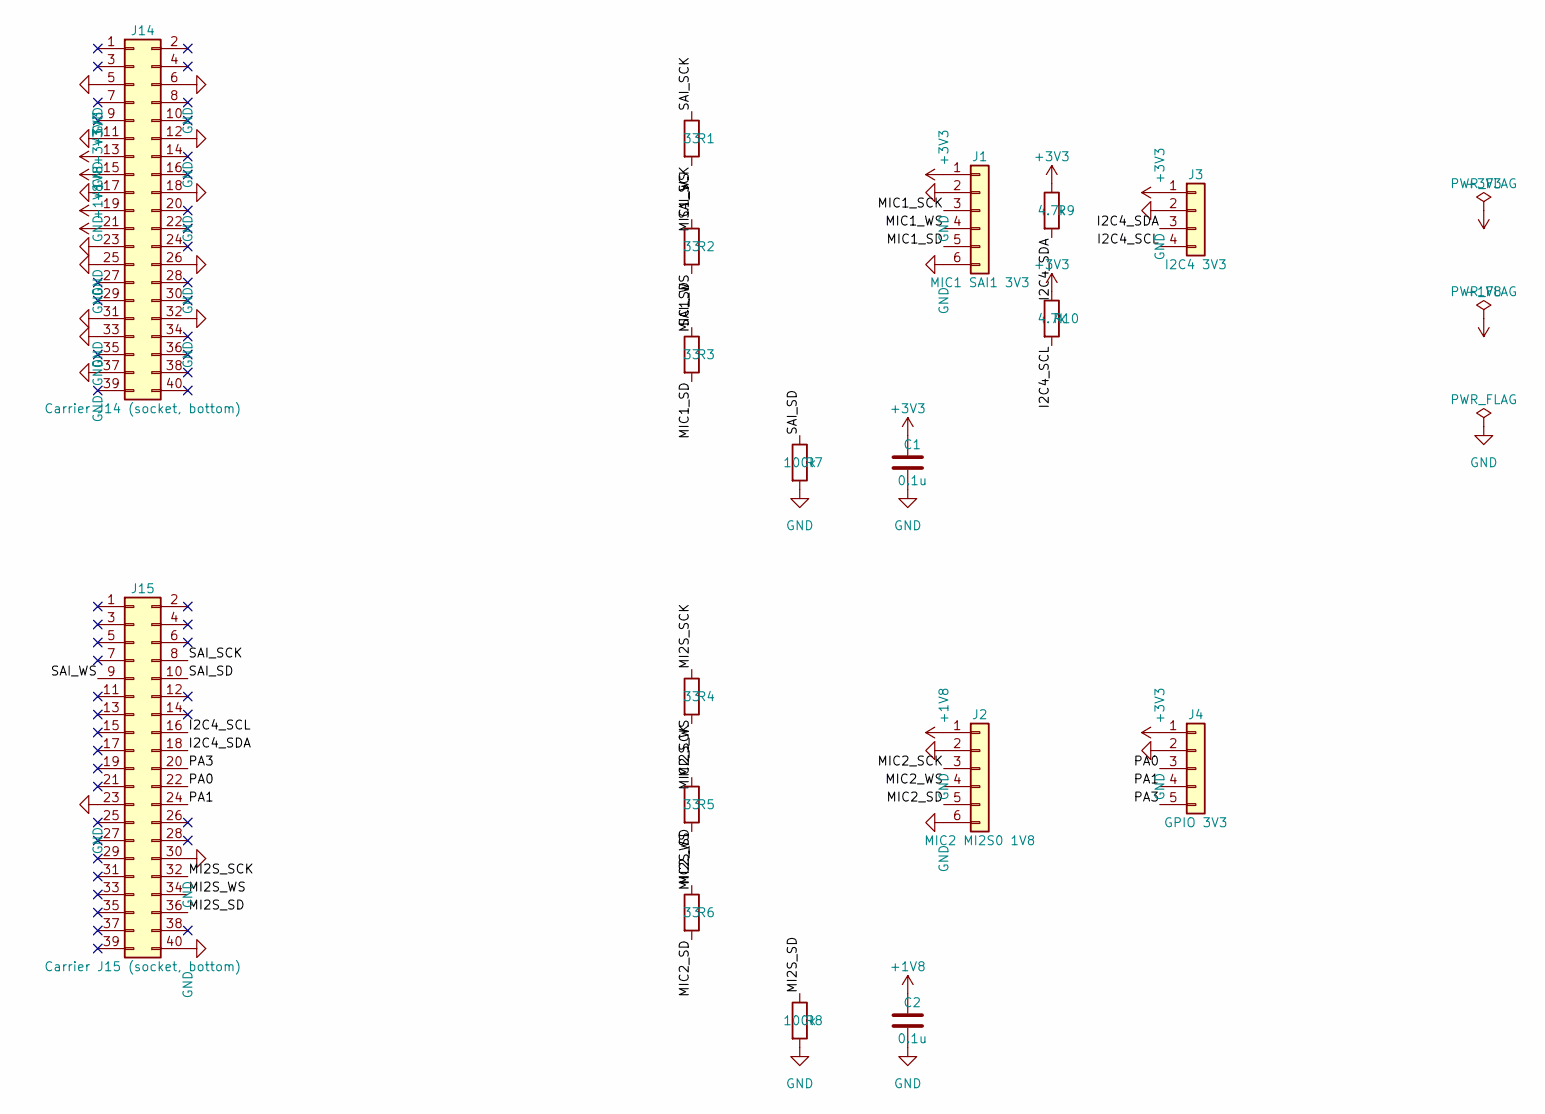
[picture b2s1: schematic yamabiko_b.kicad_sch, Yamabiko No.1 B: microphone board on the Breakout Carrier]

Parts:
C1, C2: 0.1u; C_Disc_D3.0mm_W1.6mm_P2.50mm
J1: MIC1 SAI1 3V3; JST_XH_B6B-XH-A_1x06_P2.50mm_Vertical
J2: MIC2 MI2S0 1V8; JST_XH_B6B-XH-A_1x06_P2.50mm_Vertical
J3: I2C4 3V3; JST_XH_B4B-XH-A_1x04_P2.50mm_Vertical
J4: GPIO 3V3; JST_XH_B5B-XH-A_1x05_P2.50mm_Vertical
J14: Carrier J14 (socket, bottom); PinHeader_2x20_P2.54mm_Vertical
J15: Carrier J15 (socket, bottom); PinHeader_2x20_P2.54mm_Vertical
R1, R2, R3, R4, R5, R6: 33; R_Axial_DIN0207_L6.3mm_D2.5mm_P2.54mm_Vertical
R7, R8: 100k; R_Axial_DIN0207_L6.3mm_D2.5mm_P2.54mm_Vertical
R9, R10: 4.7k; R_Axial_DIN0207_L6.3mm_D2.5mm_P2.54mm_Vertical

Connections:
+1V8: C2.1, J2.1, J14.19, J14.21
+3V3: C1.1, J1.1, J3.1, J4.1, J14.13, J14.15, R9.1, R10.1
/I2C4_SCL: J3.4, J15.16, R10.2
/I2C4_SDA: J3.3, J15.18, R9.2
/MI2S_SCK: J15.32, R4.1
/MI2S_SD: J15.36, R6.1, R8.1
/MI2S_WS: J15.34, R5.1
/MIC1_SCK: J1.3, R1.2
/MIC1_SD: J1.5, R3.2
/MIC1_WS: J1.4, R2.2
/MIC2_SCK: J2.3, R4.2
/MIC2_SD: J2.5, R6.2
/MIC2_WS: J2.4, R5.2
/PA0: J4.3, J15.22
/PA1: J4.4, J15.24
/PA3: J4.5, J15.20
/SAI_SCK: J15.8, R1.1
/SAI_SD: J15.10, R3.1, R7.1
/SAI_WS: J15.9, R2.1
GND: C1.2, C2.2, J1.2, J1.6, J2.2, J2.6, J3.2, J4.2, J14.5, J14.6, J14.11, J14.12, J14.17, J14.18, J14.23, J14.25, J14.26, J14.31, J14.32, J14.33, J14.37, J15.23, J15.30, J15.40, R7.2, R8.2

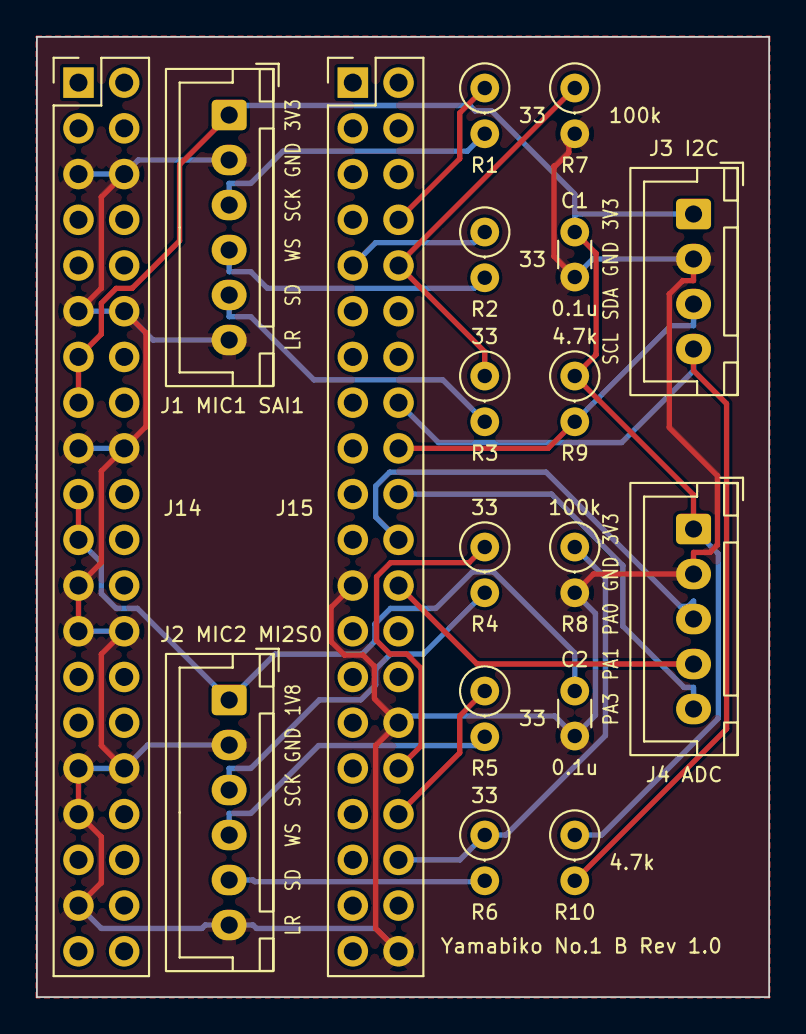
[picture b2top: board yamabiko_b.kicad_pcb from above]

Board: 2 copper layers, 40.7 x 53.3 mm, 18 parts (0 on the bottom side), 20 nets.
